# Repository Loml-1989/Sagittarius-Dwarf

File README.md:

# Sagittarius Dwarf

The VERY tiny USB C microcontroller dev board themed after the Sagittarius Dwarf Spheroidal Galaxy and the supermassive black hole Sagittarius A\* (Sgr A\*).

---
## 3D Renders (Black Hole & Space Edition)

|          Top View           |             Isometric View              |            Bottom View            |
| :-------------------------: | :-------------------------------------: | :-------------------------------: |
|  |  |  |

---

## Features
- **Very Compact Footprint:** Only 10.5mm x 10mm, barely larger than the USB C plug.

- **Microchip ATtiny1616:**
	1. 8 bit RISC microcontroller going up to 20 MHz.
	2. 16 KB Flash, annd 2 KB SRAM.

- **Addressable RGB LED:**
	1. Featuring a WS2812B RGB LED connected directly to microcontroller.

- **USB Type C Connectivity:**
	1. 16 pin USB C receptacle.

- **Exposed GPIO & Programming Test Pads:**
	- Four test points arranged along the bottom edge:
	    1. **`U`**: Single wire `UPDI` programming & debugging interface (Pin 19).
	    2. **`A3`**: GPIO pin **`PA3`** (Pin 2).
	    3. **`+`**: **`+5V`** power.
	    4. **`G`**: **`GND`** ground.

---
Dedicated to Black holes <3

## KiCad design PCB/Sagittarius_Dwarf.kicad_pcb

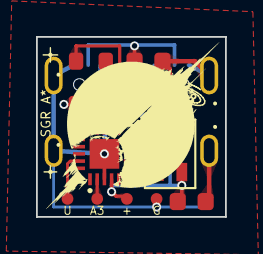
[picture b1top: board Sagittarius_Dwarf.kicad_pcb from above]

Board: 2 copper layers, 10.5 x 10.0 mm, 12 parts (1 on the bottom side), 7 nets.

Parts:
C1: 100nF; C_0603_1608Metric
C2: 22uF; C_0603_1608Metric
D1: SK6805; LED_SK6805_PLCC4_2.4x2.7mm_P1.3mm
D2: D; D_SOD-323
J1: USB_C_Receptacle_USB2.0_16P; USB_C_Receptacle_GCT_USB4105-xx-A_16P_TopMnt_Horizontal
R1, R2: 5.1k; R_0603_1608Metric
TP1: UPDI; TestPoint_Pad_D1.0mm
TP2: PA3; TestPoint_Pad_D1.0mm
TP3: +5V; TestPoint_Pad_D1.0mm
TP4: GND; TestPoint_Pad_D1.0mm
U1: ATTINY1616-MNR; QFN-20_L3.0-W3.0-P0.40-BL-EP1.7

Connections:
+5V: C1.1, C2.1, D1.4 (VDD), D2.1, J1.A4 (VBUS), J1.A9 (VBUS), J1.B4 (VBUS), J1.B9 (VBUS), TP3.1, U1.4 (VDD)
/DIN: D1.3 (DIN), U1.7 (PA6)
/PA3: TP2.1, U1.2 (EXTCLK/PA3)
/UPDI: TP1.1, U1.19 (PA0/~RESET/UPDI)
GND: C1.2, C2.2, D1.2 (VSS), D2.2, J1.A1 (GND), J1.A12 (GND), J1.B1 (GND), J1.B12 (GND), J1.SH (SHIELD), R1.2, R2.2, TP4.1, U1.3 (GND), U1.21 (EP)
unnamed: J1.A5 (CC1), R1.1
unnamed: J1.B5 (CC2), R2.1

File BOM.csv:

Designator,Component Name,Quantity,Description,Vendor Link,Est Price (USD)
U1,ATtiny1616 8-bit AVR Microcontroller,1,"16KB Flash, 2KB SRAM, 128B EEPROM, 20MHz AVR MCU",https://robu.in/product/attiny1616-mfr-microchip-8-bit-mcu-a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,$3.00
D1,Addressable Smart RGB LED,1,Intelligent digital addressable RGB LED (WS2812B protocol compatible),https://robu.in/product/sme-ws2812b-2020-addressable-rgb-pix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,$0.10
J1,USB Type-C 16-Pin Receptacle,1,USB 2.0 Type-C 16P Female Connector with GND shield tabs,https://robu.in/product/type-c-31-m-16-hroparts-1-6p-female-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,$1.00
D2,Schottky Barrier Diode 20V 0.5A,1,Schottky barrier diode for VBUS reverse polarity protection,https://robu.in/product/b0520ws-mdd-20v-independent-390mv500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,$0.15
R1,SMD Resistor 5.1k 1% 0.1W,2,CC1 USB-C 5.1k pulldown configuration resistor,https://robu.in/product/rc0603fr-0710kl-yageo-res-thick-film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,$0.10
C1,SMD Ceramic Capacitor 100nF (0.1uF) 50V X7R,1,100nF high-frequency decoupling capacitor for VBUS,https://robu.in/product/0-1uf-capacitor-smdc-0603/,$0.10
C2,SMD Ceramic Capacitor 22uF 10V/6.3V X5R,1,22uF bulk decoupling capacitor for power rail stability,https://robu.in/product/cl31a226mqhnnne-samsung-cap-ceramic-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,$0.10
PCB,Custom PCB (5 pcs),5,PCB,https://www.lioncircuits.com/,$11.00
Pan,,1,Pan for sand for reflowing solder. (diy hot plate),https://blinkit.com/prn/lazywindow-tadka-pan-with-long-steel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,$3.00
Sand,,1,Sand for diy hot plate,https://www.amazon.in/Premium-Ultra-Fine-River-Sand/dp/B0GJ5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,$2.00
Soldering Paste,,1,Soldering paste for soldering,https://makerbazar.in/products/mechanic-smd-solder-paste-flu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,$2.00
TOTAL,,,,,$25.55
